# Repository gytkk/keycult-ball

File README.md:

# keycult-ball

Keycult No.1/60에 트랙볼을 결합하기 위한 PCB와 보강판(플레이트)을 제작하는 개인 프로젝트입니다. 기존 케이스를 절삭하거나 새 구멍을 뚫지 않고, PCB와 보강판을 교체해 G/H 사이에 34mm Keyball을 배치하는 것이 목표입니다. 키 배열은 직교 배열을 사용하고, 유선 USB와 QMK 기반 키보드 및 포인팅 장치를 구현할 계획입니다.

현재는 예비 기구 배치와 **65키 및 62키 KiCad 회로도·PCB 배선 초안**을 검토하는 단계입니다. DRAFT E는 외부 조립체 DB1로 UDB C5-JSH를 그대로 사용하며, 하단 1.5u M1/M2 좌표에 맞춰 내부 회로와 매트릭스 배선을 다시 생성합니다. J1 측 USB는 F.Cu 중심 배선과 접지 귀환 경로를 적용합니다. JLC04161H-7628 후보 stackup을 CAD에 명시하고 접지 귀환 경로를 보완했으며, [USB 배선 검토](design/pcb/README.md#usb-routing-findings)에 적용 범위와 한계를 기록합니다. [KiCad 프로젝트 안내](design/pcb/README.md), 배치도, 키 중심 좌표 및 1:1 인쇄 자료가 있으며, 현재 검사 결과는 [65키 보고서](design/pcb/reports/validation.json)와 [62키 보고서](design/pcb/62/reports/validation.json)를 기준으로 합니다. 실제 케이스 조립, 센서 인터페이스, 전원 및 USB 신호 품질과 제조 적합성은 미확정입니다. 제조용 최종 CAD나 빌드·동작 검증된 QMK 펌웨어는 아직 없습니다.

보유 케이스는 NovelKeys 최신 판매 버전의 WK이며, 정확한 리비전과 과거 공개 도면의 호환성은 확인이 필요합니다. G/H 사이 중앙 통합은 필수 조건이며 외부 별도 장치는 범위에서 제외합니다. 34mm Keyball은 현재 예비 배치의 기준이고, 작은 볼과 터치패드도 중앙 통합 후보로 검토합니다. 최종 장치는 아직 선택하지 않았으며 [실현 가능성과 대안 조사](docs/feasibility.md)를 참고합니다.

[로컬 FreeCAD 보강판 초안](design/preliminary/design.md#로컬-freecad-보강판-초안)은 공식 NoLeaf 외곽에 65키·62키 좌표를 적용해 재생성하고 중앙 개구와 네 점으로 고정하는 프레임을 검토합니다. 편집용 FCStd와 STEP/DXF는 원본 사용 조건에 따라 로컬에만 생성합니다. 설명용 볼 높이에서 현재 PCB와 간섭하므로 제조용 도면은 아니며, 홀더·센서의 실제 고정부와 PCB 개구 또는 볼 높이를 추가로 결정해야 합니다. [FreeCAD 실행 및 재현 절차](docs/reproduction.md#freecad-보강판-초안)를 따릅니다.

## 현재 검토 중인 배치

추천안은 15u 너비의 5행 65키 배열이며, 중앙 3열의 가운데 3행을 비워 트랙볼 공간을 확보합니다. 하단 중앙은 1.5u M1/M2 두 키로 총 3u를 차지하며 M3 물리 키는 제거합니다. 실제 키캡과 스위치 조립 적합성은 미확정입니다. 아래 값은 현재 예비 설계의 계산값입니다.

| 항목 | 값 또는 조건 |
| --- | --- |
| 키 피치와 명목 키필드 | 19.05mm, 285.75 × 95.25mm |
| 볼과 G/H 키 중심 | 볼 `(0, 0)`, G `(-38.10, 0)`, H `(+38.10, 0)`, 단위 mm |
| 볼과 키캡 사이 최소 평면 간격 | 지름 34mm 볼과 1u 18 x 18mm, 1.5u 27.525 x 18mm 키캡 가정에서 12.10mm |
| 임시 조립 예약 영역 | 50 × 50mm, 키캡과 최소 4.10mm 간격 |
| 뒤쪽 공간 확보 옵션 | 15u 62키. 상단 중앙 Vol-/Mute/Vol+를 제거해 중앙 명목 빈 영역을 57.15 × 76.20mm로 확장 |
| 보류한 대안 | 14u 너비의 64키 배열. 같은 예약 영역과 키캡이 5.425mm 겹침 |

62키 옵션은 볼 지름 34mm와 중심, G/H 및 하단 1.5u M1/M2를 포함한 나머지 키를 유지합니다. 뒤쪽 한 행을 비워 센서와 배선, 지지 브리지와 체결 간격을 검토할 공간을 확보합니다. 키 제거만으로 강성이 좋아지는 것은 아니며, 빈 영역 전체를 절개하면 강성이 낮아질 수 있습니다. 볼을 키우거나 수직 여유를 늘리는 옵션이 아닙니다.

KiCad 원본은 65키의 `design/pcb/keycult65.*`와 62키의 `design/pcb/62/keycult62.*`로 나눕니다. 두 PCB의 MCU·전원 등 공통 회로는 이전 초안에서 왼쪽으로 76.2mm(4피치) 옮겨 뒤쪽 중앙 빈 영역을 피합니다. 65키 PCB는 중앙 50 x 50mm를 예약하고, 62키 PCB는 명목 빈 영역을 작업 외곽에 맞춰 자른 57.15 x 75.875mm를 부품·구리 금지 영역으로 둡니다. 두 영역 모두 실제 가공 구멍이나 홀더 치수가 아니며, 중앙 Edge.Cuts 개구는 없습니다. 예비 배치와 PCB는 같은 키 좌표를 사용합니다.

50 × 50mm 영역은 실제 홀더 외곽이나 보강판 및 PCB의 가공 구멍 치수가 아닙니다. 공개 도면의 초록색 경계도 공식 보강판 윤곽을 복제한 것이 아니라, 전체 치수만 참조한 285.75 × 108.25mm 직사각형입니다. 현재 검증은 이 경계 안의 포함 여부와 부품 사이 평면 간격을 확인하며, 실제 케이스 개구부 통과나 수직 공간, 조립 가능 여부를 증명하지 않습니다.

## 자료 안내

| 자료 | 내용 |
|---|---|
| [프로젝트 맥락](docs/project-context.md) | 요구사항, 결정 이유, 확정/가정/미확정, 실측·다음 단계 |
| [KiCad 65키·62키 초안](design/pcb/README.md) | 각 배열의 편집 가능한 회로도·PCB, BOM·GPIO 맵, 실제 ERC/DRC·좌표 검증 및 PDF/SVG |
| [PCB 구현 계획](docs/pcb-implementation-plan.md) | 실측 전에 진행할 회로도·PCB 초안, 단계별 산출물과 제조 전 검증 |
| [실현 가능성과 대안 조사](docs/feasibility.md) | 34mm 중앙 통합의 제약과 중앙에 통합할 소형 터치패드·트랙볼 비교 |
| [상세 설계와 출처](design/preliminary/design.md) | 치수 계산, 장착·flex, 센서 방향, QMK·USB 범위 |
| [Ploopy / Keyball / Charybdis 및 라이선스](docs/alternatives-and-licenses.md) | 제품별 차이, 원본 공개 범위와 재사용 조건 |
| [배치 HTML](design/preliminary/layout.html) · [SVG](design/preliminary/layout.svg) · [JSON](design/preliminary/layout.json) | 브라우저 설명도, 편집 가능한 벡터, 모든 키 중심 좌표 |
| [단면 SVG](design/preliminary/section.svg) · [PNG](design/preliminary/section.png) | 수직 설치 센서와 미확정 Z 스택 |
| [1:1 A3 PDF](design/preliminary/print-1to1.pdf) · [SVG](design/preliminary/print-1to1.svg) | 100mm 기준선 포함 종이 검증용 |
| [62키 옵션 SVG](design/preliminary/rear-clearance.svg) · [PNG](design/preliminary/rear-clearance.png) · [1:1 A3 PDF](design/preliminary/rear-clearance-print.pdf) · [인쇄 SVG](design/preliminary/rear-clearance-print.svg) · [인쇄 HTML](design/preliminary/rear-clearance-print.html) | 뒤쪽 공간 확보 비교. 좌표는 `layout.json`의 `rear_clearance` |
| [재현·검증 방법](docs/reproduction.md) | 좌표 생성, PNG/PDF 렌더, 원본 취득·해시 검증 |
| [에이전트 작업 지침](AGENTS.md) | 설계 변경, 검증, 공개 자료 관리, 커밋·푸시 규칙 |

HTML은 저장소를 내려받은 뒤 브라우저에서 엽니다. GitHub에서는 위 PNG로 미리 볼 수 있습니다. 종이 배치는 A3 가로, 배율 100%, 페이지 맞춤을 끈 상태로 출력하고 100mm 기준선을 자로 확인합니다.

## 생성과 검증

Python 3.11 이상과 `uv`를 사용하며, 명령은 저장소 루트에서 실행합니다. 검증 및 렌더 스크립트의 의존성은 각 파일의 메타데이터에 고정되어 있고 `uv run`이 준비합니다.

기존 산출물과 문서의 로컬 링크를 검증하려면 다음 명령을 실행합니다.

```bash
uv run scripts/validate.py
```

배열이나 치수를 변경한 경우에는 산출물을 순서대로 다시 생성하고 검증합니다.

```bash
uv run design/preliminary/build_artifacts.py
uv run scripts/render.py
uv run scripts/validate.py
```

`design/preliminary/build_artifacts.py`의 배열과 치수 상수가 편집 원본이며, 키 중심 JSON과 SVG/HTML은 생성 결과입니다. 설계 변경은 생성기에 반영합니다. 생성기만 실행하면 기존 PNG/PDF는 갱신되지 않으므로 `scripts/render.py`도 실행해야 합니다. 렌더에는 시스템 Chromium이 필요하며, PATH에서 찾을 수 없으면 `KEYCULT_CHROMIUM`에 실행 파일의 절대 경로를 지정합니다.

검증 스크립트는 파일 형식과 로컬 링크, 키 개수와 좌표, 평면 간격, 직사각형 경계 안의 포함 여부, PDF의 A3 크기와 100mm 기준선을 검사합니다. 검증 결과 일부는 `envelope-containment.json`과 `print-validation.json`에 기록됩니다.

공식 윤곽 검사는 별도 절차입니다. 원본 사용 조건을 확인한 뒤 `uv run scripts/fetch_sources.py`로 원본을 취득하고 `uv run scripts/verify_official_contour.py`로 재현합니다. [과거 검사 기록](design/preliminary/plate-containment.json)은 현재 공개 검증으로 갱신되지 않습니다. 추출 좌표와 재검사 출력의 저장 위치, 해시 확인 방법은 [재현 문서](docs/reproduction.md)를 따릅니다.

## 다음 설계 단계

1. [65키·62키 KiCad 초안](design/pcb/README.md)의 실제 ERC/DRC와 미배선 보고서를 검토하고, USB·클록·전원 배선 품질을 보완합니다. GH60의 285.0 x 94.6mm 요약 치수를 작업 외곽으로 사용하며 배열별 중앙 예약 영역에 부품과 구리를 두지 않습니다. USB는 UDB C5-JSH와 적절한 길이의 1:1 케이블을 사용하는 설계 가정으로 진행하고, 조립 전에 커넥터와 케이스 공간 및 케이블 도통을 확인합니다. 센서는 정확한 사양이 확인될 때까지 논리 패드로 남깁니다.
2. QMK 핀맵과 펌웨어 빌드를 병행하고, 실물 부품과 배선 조건이 확인되면 단일 USB 동작을 시험합니다.
3. 후속 실측과 종이 배치 검토를 반영해 중앙 개구, 커넥터와 부품 높이 및 장착 구조를 확정합니다. 볼과 센서는 같은 강체에 고정하고, 기구 시제품 검증 후 최종 배선과 제조 데이터를 완성합니다.

측정할 항목과 결정 이유는 [프로젝트 맥락](docs/project-context.md)에 기록합니다. 예비 SVG를 제조용 도면으로 사용하지 않습니다.

## 범위와 출처 관리

공개 자료는 독립 키 배열, 형상을 복제하지 않는 요약 측정값, 검증 결과, 출처 URL과 해시입니다. 제3자 STEP/DXF/Gerber 원본, 공식 보강판 윤곽 좌표와 이를 복제한 도면은 공개하지 않습니다. 원본 다운로드는 `design/preliminary/sources/upstream/`에, 상세 윤곽과 로컬 검사 결과는 `design/preliminary/sources/local/`에 저장하며 두 디렉토리는 Git에서 제외합니다. 원본 대화, 개인 메모, 인증 정보도 포함하지 않습니다.

저장소 공개 자체가 제3자 자료의 재사용이나 재배포 허가를 뜻하지 않습니다. 자료를 취득하거나 재사용하기 전에 [자료별 라이선스와 배포 범위](docs/alternatives-and-licenses.md), [출처와 측정 기록](design/preliminary/sources/README.md)을 확인합니다.

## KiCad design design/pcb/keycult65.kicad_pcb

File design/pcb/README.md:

# Keycult65 and Keycult62 KiCad designs

**DRAFT E, not for fabrication or assembly.** Both variants use the same RP2040 circuit and stable key references. Open the corresponding project in **KiCad 10.0.7**. The schematic and PCB are native editable CAD.

| Variant | Project | Schematic | PCB | Validation |
| --- | --- | --- | --- | --- |
| 65 keys | [keycult65.kicad_pro](keycult65.kicad_pro) | [Schematic](keycult65.kicad_sch) | [PCB](keycult65.kicad_pcb) | [Report](reports/validation.json) |
| 62 keys | [keycult62.kicad_pro](62/keycult62.kicad_pro) | [Schematic](62/keycult62.kicad_sch) | [PCB](62/keycult62.kicad_pcb) | [Report](62/reports/validation.json) |

Both variants pass strict validation after regeneration and saved-route replay: zero ERC violations, DRC violations, unconnected items and schematic/PCB mismatches. The reports contain the counts and CAD hashes. Static electrical checks do not establish powered operation or case fit. The user-approved design assumption is an unmodified external UDB C5-JSH, represented by DB1 in the schematic and assembly BOM, with no footprint on the main PCB. J1 implements its 1:1 cable interface. The sensor interface remains logical pads pending hardware identification.

## Review entry points

- [Native schematic](keycult65.kicad_sch), [native PCB](keycult65.kicad_pcb), [project](keycult65.kicad_pro).
- [Schematic PDF](exports/schematic.pdf), [front copper SVG](exports/front.svg), [back copper SVG](exports/back.svg), [ground plane SVG](exports/ground.svg), [layer PDF](exports/board-layers.pdf).
- 62-key exports: [schematic PDF](62/exports/schematic.pdf), [front](62/exports/front.svg), [back](62/exports/back.svg), [ground plane](62/exports/ground.svg), [layer PDF](62/exports/board-layers.pdf), [BOM](62/bom.csv), [key/GPIO map](62/gpio-map.csv).
- [Real validation summary](reports/validation.json), [KiCad ERC](reports/erc.json), [KiCad DRC including native schematic parity](reports/drc.json), [actual exported netlist](reports/netlist.xml).
The layer PDF is auto-fitted for review, **not a 1:1 print or manufacturing template**.

- [BOM with candidates/uncertainties](bom.csv), [key/GPIO map](gpio-map.csv), [QMK pin reference](qmk-config.h.example), [source/license record](sources.md).

## Implemented electrical content

65 or 62 MX PCB-mount solder switches and individual 1N4148W diodes. Cathode/pad 1 is
the ROW net; current path is COL → switch → diode anode → cathode → ROW. QMK
`COL2ROW`, five rows × fifteen columns; ten intersections are absent in the 65-key variant and thirteen in the 62-key variant. IDs, not labels, identify keys because labels repeat.

Both variants omit bottom-row SW59/D59 and retain SW58/D58 and SW60/D60 as the 1.5u M1/M2 keys, preserving IDs r4c6/r4c8 and removing r4c7. Their layout centres are (-14.2875,38.1)mm and (14.2875,38.1)mm, occupying a combined nominal 3u. The M3 physical key has no replacement mapping yet. The 62-key variant also omits SW7-SW9 and D7-D9 without renumbering other parts. COL6 and COL8 remain connected to the bottom keys; COL7 has no key in the 62-key variant, so GP16 is marked NC in its schematic. The shared 15-column GPIO ordering is retained; all COL7 matrix cells must be KC_NO in eventual firmware. Removing only the three switches from a functioning 65-key board leaves open matrix cells; map those positions to `KC_NO` in the eventual firmware. Cutting the PCB is a separate mechanical and copper change, never implied by switch removal.

RP2040 is directly mounted in its 7×7mm QFN, not represented by a development
board. The design includes AP2112K-3.3, input PTC, input/output bulk capacitors,
individual IOVDD/ADC/USB/core decoupling, the internal 1.1V regulator's 1µF caps,
W25Q16JVSSIQ QSPI flash, QSPI clock resistor, CS pull-up, BOOTSEL through 1kΩ,
12MHz ABM8-272-T3 oscillator with 15pF load caps and 1kΩ drive resistor, USB 27Ω
series resistors, RUN pull-up/reset button, and individual SWD pads. TESTEN is
GND. Unused GPIOs and regulator NC have explicit no-connect marks.

**W25Q16JVSSIQ uses the 208mil/5.3mm SOIC footprint**, not a similarly named
150mil SOIC. Passive MPNs, capacitor bias derating, crystal drive/startup and
supply thermal/load budgets remain a procurement/bring-up review, not claims of
qualification. No power LED was added. PTC hold rating does not authorize a
500mA USB device or prove USB descriptor/inrush compliance.

### GPIO budget

| Purpose | RP2040 GPIO |
|---|---|
| SPI0 MISO / CS / SCLK / MOSI | GP0 / GP1 / GP2 / GP3 |
| Rows 0–4 | GP4, GP5, GP6, GP7, GP8 |
| Columns 0–14 | GP9–GP22, GP26; GP16/COL7 is NC in the 62-key variant |
| Optional sensor motion / reset | GP23 / GP24 |
| Explicit unused/NC | GP25 / GP27 / GP28 / GP29; also GP16 in the 62-key variant |

The 65-key variant allocates 26 of 30 GPIOs, including two optional sensor controls; four remain
unused. The 62-key variant allocates 25, leaving five NC. Dedicated QSPI, USB and SWD pins do not consume these 30 GPIOs.
`qmk-config.h.example` is a mapping aid, **not a compiled QMK port**. It does not
select a sensor revision, flash boot stage, descriptor power or a final keymap.

## USB daughterboard interface and compatibility limits

**J1 is a JST SM04B-SRSS-TB(LF)(SN), a 4-contact, 1.00mm-pitch side-entry header on B.Cu.** The [Wilba WT60-D product documentation](https://salvun.com/products/wilba-60-pcb-wt60-d) explicitly identifies its JST connection as UDB-compatible and lists Keycult No.1/60 compatibility after removing the on-board USB connector and fitting JST. The [UDB designer specification](https://github.com/Unified-Daughterboard/UDB-C-Legacy/wiki/PCB-side-design-resources) and [pinned C3 schematic](https://github.com/Unified-Daughterboard/UDB-C-Legacy/blob/2ecdd7e0482ecbd3ffe9af04966ab3555f7fc33c/KiCad/C3/Unified-Daughterboard.sch) establish the connector and pinout. This supports the UDB electrical design target; it does not identify the user's uninspected daughterboard as a particular UDB revision.

| J1 contact | Signal | Existing test pad |
| --- | --- | --- |
| 1 | VBUS_USB, after C5-JSH protection and before main-board F1 | TP1 |
| 2 | USB_DM, D- | TP3 |
| 3 | USB_DP, D+ | TP4 |
| 4 | GND | TP2 |
| MP | Mechanical solder anchors, tied to GND locally | Not a cable contact |

Use a **1:1 contact-number cable**, 1-to-1 through 4-to-4. Wire color and apparent left-to-right order are not pin-number evidence. TP1-TP4 retain their earlier numbering and are test access, not the connector's contact order. The validator independently checks J1 against the UDB map, including rejection of reversed power and swapped data contacts.

J1's footprint origin is PCB **(40.6,112.0)mm**, B.Cu, rotation 90 degrees, with its mouth facing keyboard-left. Looking down from the switch side, pad centres are x=42.6mm and y=113.5,112.5,111.5,110.5mm for contacts 1-4. The [official WT60-A photo](https://keycult.com/products/wt60-a-pcb-60) supports a left-edge connector facing outward, but supplies no exact coordinates. Our position is an independent placement between the ortholinear switch/diode footprints, **not a measured WT60-A connector registration**. Case-channel alignment, mating clearance and the connector's full installed height below the PCB need physical checking. JST specifies a nominal 2.9mm body height; do not infer assembled clearance from the footprint courtyard alone.

J1's data pair runs on F.Cu along the left and top margins, above the In1.Cu ground pour, with short B.Cu escapes at J1, TP3/TP4 and R1/R2. Connector-side USB traces are 0.29mm wide; the paired F.Cu portions have a 0.2mm edge gap. VBUS retains its separate 0.4mm feed to the main-board fuse. The MCU-side USB traces and component placement are unchanged.

The 2026-10-30 resume review measured the saved native PCB segments in both variants. Their USB copper is identical. Lengths below are the sum of segment centreline lengths, including branches to test pads; they exclude pad traversal, via barrels and the external cable, so they are not end-to-end electrical lengths.

| Saved copper | D- | D+ |
| --- | --- | --- |
| J1-side net, before the series resistor | 151.4028mm | 157.3721mm |
| F.Cu portion of J1-side net | 146.5028mm | 150.4615mm |
| B.Cu portion of J1-side net | 4.9000mm | 6.9107mm |
| Vias on the J1-side net | 4 | 4 |
| MCU-side net, after the series resistor | 6.6253mm | 6.6253mm |

The J1-side segment-sum difference is 5.9693mm. These are measured routing properties, not acceptance limits or evidence of signal-integrity failure. A USB netclass records the 0.29mm width and 0.2mm gap for these two nets. The candidate dielectric model and the limits of the impedance calculation are described under [USB routing findings](#usb-routing-findings).

Strict validation refills zones and checks the full-width projection of every F.Cu USB segment against the saved In1.Cu GND polygons. Both variants have zero uncovered area outside explicit 0.51mm-radius disks around USB transition vias. Those disks exclude signal-via antipads, not unrelated voids elsewhere on the route. The measured minimum F.Cu pair edge gap is 0.2mm. The layer PDF supports inspection of the J1 escape, margin pair, test pads, resistor transitions and ground fill. These geometric checks do not qualify finite plane edges, transitions or cable discontinuities.

DRAFT E uses a regenerated base route for the current 1.5u M1/M2 coordinates. After SES import, `scripts/usb_routing.py` applies the connector-side USB recipe and ground changes. Validation uses official KiCad 10.0.7 in a local Docker container. The route manifest includes this script's hash. Native schematic parity, external DB1 netlist, coordinates and central reservations are checked again. Both variants have fresh native PDF/SVG exports and validation reports.

DB1 is the unmodified [C5-JSH at revision `2b6c52aa2de6f9f60ca99c6250e4bdf01e8f4eea`](https://github.com/Unified-Daughterboard/UDB-C-JSH/blob/2b6c52aa2de6f9f60ca99c6250e4bdf01e8f4eea/UDB.kicad_sch), adopted as a design assumption on 2026-10-30. Its USB-C connector, two 5.1k CC pull-downs, TPD4E05U06DQAR data-line ESD array, ASMD1206-150 PTC and SMF6.0A TVS stay on the external daughterboard. Its shield joins signal ground on that board; no extra shield wire, CC resistors or duplicate ESD/TVS array is added to the main PCB. This assumption is not a measurement of the factory Keycult board.

Main-board F1 remains a 500mA-hold PTC for local protection, and R1/R2 remain the RP2040's 27-ohm USB series resistors. The two PTCs are in series, so their total voltage drop, trip coordination and actual load/inrush need verification. The TVS suppresses transients; this design has no active sustained-overvoltage disconnect. DB1's BOM row is an external assembly requirement, not a component to populate on the main PCB.

The WT compatibility research supports continuing with the existing J1 pin map. [WT60-C's product documentation](https://dailyclack.com/products/wt60-c-kate-60-pcb) explicitly specifies the same JST part and UDB compatibility; WT60-D does likewise for the interface, and the [Keycult FAQ](https://resources.keycult.com/faq_keycult_faq.html) lists WT60-G for No.1/60. This evidence establishes the design interface without requiring a measurement of the stock cable. It does not establish that every WT-family or Keycult daughterboard contains the same protection components. [Pinned circuit evidence](sources.md#usb-daughterboard-evidence) records the UDB revision differences.

As confirmed by the user on 2026-10-30, a suitable cable length can be sourced; stock-cable reach is no longer a design constraint. Before powered assembly, verify the selected cable's four contact paths and that the assembled external board matches the assumed C5-JSH design. Connector insertion, routing and bend clearance remain mechanical checks in issue #3. Factory-board identification is not a prerequisite for circuit design under this explicit assumption.

## Power and USB desk review

The 2026-10-30 [calculated report](reports/electrical-review.json) records conditional power estimates and native measurements for both boards. It is separate from ERC/DRC and grants no electrical or manufacturing pass. [Primary sources](sources.md#electrical-desk-review-sources) identify the component revisions and public stackups. DRAFT E applies the 7628 routing-study geometry; the provisional power allocations remain assumptions and do not change components or authorize a particular sensor.

### Power allocation

Use **150mA total on +3V3 as a provisional planning envelope**. Allocate 80mA to RP2040, 25mA to flash and 5mA to other board loads, leaving **40mA for a future 3.3V sensor**. The MCU and miscellaneous numbers are engineering allowances, not guaranteed maxima. Flash current depends on frequency and output loading; the 25mA allowance requires checking the cited conditions and a read clock no greater than 104MHz. A 5V Keyball module cannot be assessed using the 40mA rail allowance directly. Its supply, regulators and level translation remain unresolved.

The model reserves another 1mA for LDO ground current, giving 151mA input before external-board leakage. This is an assumption; AP2112's 80uA maximum is a no-load specification. The configured USB power declaration must cover the final whole-device load. The 110mA main-board allocation does not demonstrate compliance with the 100mA pre-configuration limit. Startup and the 2.5mA suspend limit need separate firmware budgets; no power-switching or suspend implementation is claimed here.

Heat screening assumes 5.5V input, nominal 3.3V output, no upstream voltage drop, 1mA LDO ground current, 50 C local ambient and the datasheet's 184 C/W junction-to-ambient resistance. This resistance is a reference condition, not a measurement of this PCB or the closed case.

| +3V3 load | Calculated LDO loss | Estimated junction temperature |
| --- | --- | --- |
| 100mA | 0.2255W | 91.5 C |
| 150mA | 0.3355W | 111.7 C |
| 200mA | 0.4455W | 132.0 C |
| 300mA | 0.6655W | 172.5 C |

Values beyond device limits indicate unsuitable modeled operating points, not predictions of continued operation. A chosen 125 C planning ceiling permits approximately 183mA under these assumptions, so 150mA retains some modeled margin. At 60 C ambient the 150mA estimate is 121.7 C. Higher final load or temperature requires reconsidering the regulator and layout. The 500mA-hold fuse and 600mA regulator labels are not an available continuous power budget.

The two PTC reference-temperature R1max values sum to 1.03ohm. At 151mA, adding 0.5/1.0/2.0ohm for the remaining internal supply/return path gives drops of 0.231/0.307/0.458V. From an assumed 4.4V at the daughterboard receptacle, the LDO sees approximately 4.169/4.093/3.942V. This is a low-voltage stress scenario, not permission to draw 151mA from a low-power port. External USB cable drop is already represented by receptacle voltage; hot PTC resistance is not bounded by the reference values. Nominal 3.3V plus 0.2V dropout is only a screening threshold. Actual regulation must satisfy the RP2040 USB_VDD minimum of 3.135V and flash supply maximum of 3.6V, among the other component conditions.

Native capacitor sums are 1.0uF on VBUS_FUSED, 2.9uF on +3V3 and 1.2uF on +1V1. They omit external-board/sensor capacitance and do not model tolerance, DC bias, regulator startup or active current. Nominal capacitor sums cannot establish an inrush pass.

### USB routing findings

Both variants use identical connector-side USB geometry and an explicit JLC04161H-7628 candidate copper/dielectric model: nominal 1.6mm board, 0.035mm outer copper, 0.0152mm inner copper, 0.2104mm outer-to-inner prepreg with Er=4.4, and a 1.065mm core with Er=4.6. The long pair now runs on F.Cu, 0.2104mm above In1.Cu GND. B.Cu escapes total 4.9mm for D- and 6.91mm for D+ and still lack a continuous adjacent reference plane. Their discontinuities remain part of the signal-integrity review.

Three added GND vias at PCB `(38.5,113.2)`, `(113.4,55.7)` and `(118.5,54.7)mm` join local B.Cu ground patches to In1.Cu. The resistor-side transitions use the existing GND via near `(117.312,66.595)mm`. All eight USB vias are within 2.295mm of a GND via. Validation enforces a 3mm project study criterion, not a USB specification limit. Three B.Cu ground patches and the In1.Cu top-boundary extension from y=53.2mm to y=52.96mm are included in the native zone refill and DRC.

The **JLC04161H-7628 model is applied as a routing-study assumption**, not an approved manufacturing order. JLC04161H-3313 remains a comparison only. Approximate uncoated microstrip calculations at 0.2mm edge gap give:

| Candidate | F.Cu width 0.2mm | Trial F.Cu width | Trial differential impedance |
| --- | --- | --- | --- |
| JLC04161H-7628 | 108.7ohm | 0.29mm | 90.3ohm |
| JLC04161H-3313 | 76.9ohm | 0.16mm | 89.2ohm |

The 90.3ohm result applies to an idealized uniform F.Cu section. It omits solder mask, etched trace shape, finite plane edges, nearby copper, tolerances and transitions. The top outer trace edge is only about 0.395mm inside the modeled ground boundary, so finite-plane effects need review. The CAD stackup records copper and dielectric layers only; it does not specify a fabrication mask construction. Obtain fabricator-approved geometry before treating 0.29mm as a final controlled-impedance width. Strict DRC and ground projection checks passed after routing; they do not measure impedance or establish USB compliance.

The remaining electrical work includes fabricator review and firmware startup/suspend budgets. Sensor integration, actual PTC/cable resistance, thermal measurements, inrush and full-speed waveform tests remain open. The eventual cable construction and length must be included in signal-quality validation.

## Sensor interface remains unresolved

**TP10–TP17 are MCU-side 3.3V logical/test pads only.** They are not the Keyball
7-pin connector. There is no 5V sensor feed, no sensor connector and no approved
5V module-to-RP2040 path. Exact module revision, supply, signal levels and the
appropriate translator/interface remain open in issue #2. Do not wire these
pads straight to an unverified sensor. Reset/motion are reserved, not mandatory
PMW3360 connections. The sensor connector is not finalized; J1's electrical routing is complete but its case and cable fit is provisional.

## Geometry and construction assumptions

- Layout `(0,0)` maps to PCB **(180,100)mm**, +X right, +Y toward the bottom row. Coordinates come from `../preliminary/layout.json`, using `preferred.keys` for 65 keys and `rear_clearance.keys` for 62 keys.
- Stock `SW_Cherry_MX_1.00u_PCB` and `SW_Cherry_MX_1.50u_PCB` have their anchor at **electrical pin 1**, not the
  stem. The stem NPTH is local `(-2.54,+5.08)mm`; generation compensates and
  validation reads the actual stem holes. The base pitch is 19.05mm; the two bottom 1.5u key centres are 28.575mm apart.
- Both variants move the common MCU, flash, clock, power and interface-pad group 76.2mm left from the original draft, with decoupler positions adjusted separately. The original SW7-SW9 area contained essential electronics; the original board must not be cut to obtain the 62-key variant.
- The **285.0 × 94.6mm** working rectangle uses only scalar dimensions measured
  from the pinned GH60 PCB. It does **not** copy GH60's rounded corners/holes,
  any Keycult contour, or the 285.75×108.25mm plate reference rectangle.
- The 65-key all-copper-layer rule area is the centred **50 x 50mm** reservation. The 62-key rule area extends across the nominal empty key band, clipped at the board edge: PCB x=151.425..208.575mm, y=52.7..128.575mm, **57.15 x 75.875mm**. Both prohibit footprints, pads, tracks, vias and copper fill. Neither is an Edge.Cuts opening or a measured holder outline. This larger electrical reservation preserves future placement flexibility; mounting and any eventual cutout still require measurements.
- Four copper layers: F.Cu and B.Cu plus In2.Cu carry most signals. In1.Cu carries the GND reference pour outside the reserved centre, with short local +3V3 and COL12 routes beside the MCU. These routes stay away from the USB pair and the filled ground remains connected. Pad/via antipads and the central reservation still require return-path review; this is not an
  impedance-qualified stackup. Bottom SMT electronics coexist
  with top MX switch bodies, with actual drill/courtyard checks. Board thickness
  is nominally 1.6mm in the candidate model, not a verified case height requirement.
- Review rules are 0.15mm clearance/minimum trace, 0.55-0.6mm via copper diameter with 0.3mm drill, and 0.25mm
  hole/copper-edge clearance. These are **draft routing constraints, not a
  selected manufacturer's process approval**. 0.4mm pitch QFN fan-out, solder
  mask, assembly tolerances and stackup need explicit manufacturing review.
- USB routes need a paired 90Ω differential/return-path review against a chosen
  stackup. Mere routed connectivity or DRC clearance does not establish signal
  integrity. QSPI/crystal/decoupling placement and path lengths need layout
  engineering review before a fabrication release.
- [3D check record](reports/3d-review.json) describes the original draft only. Neither revised variant has component-height or case-assembly approval. The current CLI environment omits component 3D libraries.
- STEP models are linked from installed KiCad stock libraries; no Keycult case
  or sensor assembly STEP is redistributed. A valid 2D board does **not** prove
  Z-stack, actuator clearance, cable bend space, assembly access or case fit.

## Reproduction

The initial seed uses KiCad's maintained `pcbnew` API and installed stock
libraries. `sexpdata` serializes the native schematic with stock symbols and applies the deterministic USB overlay to native PCB data. No custom autorouter was written.
Freerouting performs local detailed routing via KiCad's Specctra DSN/SES API.
A small cleanup script removes only KiCad-reported dead-ended copper after zone refill; it never suppresses checks or unconnected nets. Native CAD retains the complete editable route. Each variant's saved SES records the base route for its current key coordinates. `scripts/usb_routing.py` applies the DRAFT E USB and ground changes after seed generation and SES import. Replaying the SES through `route_pcb.py` reproduces the combined route; rerunning the autorouter from a new seed does not replace layout review or guarantee completion.
See [sources](sources.md) for versions, licenses and hashes.

From the repository root, with the Python version matching KiCad's installed binding (the original Nix runtime uses Python 3.14; the official 10.0.7 Docker image uses Python 3.13). Scripts require Python 3.11 or newer, but `pcbnew` must match the chosen interpreter. Use the [Docker procedure](../../docs/reproduction.md#docker에서-kicad-검증) when KiCad is not installed on the host.

```bash
uv run --python "$(command -v python3)" scripts/build_pcb.py --keys 65
uv run --python "$(command -v python3)" scripts/route_pcb.py --keys 65 --import-saved
uv run --python "$(command -v python3)" scripts/validate_pcb.py --keys 65
uv run --python "$(command -v python3)" scripts/build_pcb.py --keys 62
uv run --python "$(command -v python3)" scripts/route_pcb.py --keys 62 --import-saved
uv run --python "$(command -v python3)" scripts/validate_pcb.py --keys 62
uv run scripts/test_pcb_validation_gate.py
uv run scripts/validate.py
```

**Regeneration overwrites the current CAD seed.** The delivered native CAD is the
review/edit surface; preserve manual edits before rebuilding. The preliminary
layout generator remains the source for key coordinates. A changed layout
requires a new seed, route and inspection, not reuse of an old route snapshot.
The saved route is a reproducible initial draft, not a promise that arbitrary
edits autoroute the same way. Validation writes actual check reports and native
SVG/PDF exports; it does not mask or exclude violations. Running validation
without `--draft` returns nonzero for *any* DRC finding or unconnected item.

## Independent layout review findings

- The original draft had 57 unconnected items across 27 nets. Both revised variants complete the internal circuit and matrix routing, with zero unconnected items after rebuilding and replaying their saved copper.
- The original C13/C14 placement was 16.60/17.52mm from the MCU supply pads; these capacitors and the core decouplers have been repositioned beside their actual rotated supply pins.
- F1's MF-PSMF050X-2 candidate requires an 0805 land pattern; the original 1206 footprint has been corrected.
- USB impedance and return paths still require review against a selected stackup and the actual daughterboard/cable before bring-up. Connectivity alone is not signal-integrity qualification.
- The exposed MCU ground pad has a 0.3mm ground via. Via tenting/filling and solder-paste process must be agreed with the assembler to control solder loss; static DRC does not qualify QFN assembly.
- Local In1.Cu exceptions use 0.15mm traces: +3V3 runs `(102.32,64) -> (103,64.25) -> (106.2,64.25) -> (106.979,65.6)`; COL12 escapes through `(102.35,67.25) -> (102.35,65.5) -> (101.8,64.8) -> (98.7,64.8)`, in PCB mm. The signal is a keyboard column, not USB or QSPI. These short routes trade local ground-plane area for feasible QFN escape routing; the connected pour and USB reference region must be preserved in later edits.
- Draft validation permits unfinished connections only. Any geometric DRC
  finding fails in both strict and draft modes.

## Release gates still open

Issues #1–#6 remain the mechanical/interface/bring-up gate. No Gerber fabrication
release, production BOM, final sensor connector, module-level translator, firmware
build, USB/keyboard/sensor bench test or assembly-fit approval is supplied.
Read the exact outstanding electrical/route counts in each variant's `reports/validation.json`;
a zero ERC or a matching netlist is not a manufacturing-ready assertion.

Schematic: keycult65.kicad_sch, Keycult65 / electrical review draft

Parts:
C1, C2: 1uF; C_0603_1608Metric
C3, C4, C5, C6, C7, C8, C9, C10, C11, C12, C15: 100nF; C_0402_1005Metric
C13, C14: 1uF; C_0402_1005Metric
C16, C17: 15pF; C_0402_1005Metric
D1, D2, D3, D4, D5, D6, D7, D8, D9, D10, D11, D12, D13, D14, D15, D16, D17, D18, D19, D20, D21, D22, D23, D24, D25, D26, D27, D28, D29, D30, D31, D32, D33, D34, D35, D36, D37, D38, D39, D40, D41, D42, D43, D44, D45, D46, D47, D48, D49, D50, D51, D52, D53, D54, D55, D56, D57, D58, D60, D61, D62, D63, D64, D65, D66: 1N4148W; D_SOD-123
DB1: UDB C5-JSH / EXTERNAL
F1: 500mA hold / provisional; Fuse_0805_2012Metric
J1: USB / C5-JSH JST-SH; JST_SH_SM04B-SRSS-TB_1x04-1MP_P1.00mm_Horizontal
R1, R2, R7: 27R; R_0402_1005Metric
R3, R5, R8: 10k; R_0402_1005Metric
R4, R6: 1k; R_0402_1005Metric
SW1: r0c0 Esc; SW_Cherry_MX_1.00u_PCB
SW2: r0c1 1; SW_Cherry_MX_1.00u_PCB
SW3: r0c2 2; SW_Cherry_MX_1.00u_PCB
SW4: r0c3 3; SW_Cherry_MX_1.00u_PCB
SW5: r0c4 4; SW_Cherry_MX_1.00u_PCB
SW6: r0c5 5; SW_Cherry_MX_1.00u_PCB
SW7: r0c6 Vol-; SW_Cherry_MX_1.00u_PCB
SW8: r0c7 Mute; SW_Cherry_MX_1.00u_PCB
SW9: r0c8 Vol+; SW_Cherry_MX_1.00u_PCB
SW10: r0c9 6; SW_Cherry_MX_1.00u_PCB
SW11: r0c10 7; SW_Cherry_MX_1.00u_PCB
SW12: r0c11 8; SW_Cherry_MX_1.00u_PCB
SW13: r0c12 9; SW_Cherry_MX_1.00u_PCB
SW14: r0c13 0; SW_Cherry_MX_1.00u_PCB
SW15: r0c14 Bksp; SW_Cherry_MX_1.00u_PCB
SW16: r1c0 Tab; SW_Cherry_MX_1.00u_PCB
SW17: r1c1 Q; SW_Cherry_MX_1.00u_PCB
SW18: r1c2 W; SW_Cherry_MX_1.00u_PCB
SW19: r1c3 E; SW_Cherry_MX_1.00u_PCB
SW20: r1c4 R; SW_Cherry_MX_1.00u_PCB
SW21: r1c5 T; SW_Cherry_MX_1.00u_PCB
SW22: r1c9 Y; SW_Cherry_MX_1.00u_PCB
SW23: r1c10 U; SW_Cherry_MX_1.00u_PCB
SW24: r1c11 I; SW_Cherry_MX_1.00u_PCB
SW25: r1c12 O; SW_Cherry_MX_1.00u_PCB
SW26: r1c13 P; SW_Cherry_MX_1.00u_PCB
SW27: r1c14 \; SW_Cherry_MX_1.00u_PCB
SW28: r2c0 Caps; SW_Cherry_MX_1.00u_PCB
SW29: r2c1 A; SW_Cherry_MX_1.00u_PCB
SW30: r2c2 S; SW_Cherry_MX_1.00u_PCB
SW31: r2c3 D; SW_Cherry_MX_1.00u_PCB
SW32: r2c4 F; SW_Cherry_MX_1.00u_PCB
SW33: r2c5 G; SW_Cherry_MX_1.00u_PCB
SW34: r2c9 H; SW_Cherry_MX_1.00u_PCB
SW35: r2c10 J; SW_Cherry_MX_1.00u_PCB
SW36: r2c11 K; SW_Cherry_MX_1.00u_PCB
SW37: r2c12 L; SW_Cherry_MX_1.00u_PCB
SW38: r2c13 ;; SW_Cherry_MX_1.00u_PCB
SW39: r2c14 Enter; SW_Cherry_MX_1.00u_PCB
SW40: r3c0 Shift; SW_Cherry_MX_1.00u_PCB
SW41: r3c1 Z; SW_Cherry_MX_1.00u_PCB
SW42: r3c2 X; SW_Cherry_MX_1.00u_PCB
SW43: r3c3 C; SW_Cherry_MX_1.00u_PCB
SW44: r3c4 V; SW_Cherry_MX_1.00u_PCB
SW45: r3c5 B; SW_Cherry_MX_1.00u_PCB
SW46: r3c9 N; SW_Cherry_MX_1.00u_PCB
SW47: r3c10 M; SW_Cherry_MX_1.00u_PCB
SW48: r3c11 ,; SW_Cherry_MX_1.00u_PCB
SW49: r3c12 .; SW_Cherry_MX_1.00u_PCB
SW50: r3c13 /; SW_Cherry_MX_1.00u_PCB
SW51: r3c14 Shift; SW_Cherry_MX_1.00u_PCB
SW52: r4c0 Ctrl; SW_Cherry_MX_1.00u_PCB
SW53: r4c1 GUI; SW_Cherry_MX_1.00u_PCB
SW54: r4c2 Alt; SW_Cherry_MX_1.00u_PCB
SW55: r4c3 Fn; SW_Cherry_MX_1.00u_PCB
SW56: r4c4 Space; SW_Cherry_MX_1.00u_PCB
SW57: r4c5 Del; SW_Cherry_MX_1.00u_PCB
SW58: r4c6 M1; SW_Cherry_MX_1.50u_PCB
SW60: r4c8 M2; SW_Cherry_MX_1.50u_PCB
SW61: r4c9 Bksp; SW_Cherry_MX_1.00u_PCB
SW62: r4c10 Space; SW_Cherry_MX_1.00u_PCB
SW63: r4c11 Fn; SW_Cherry_MX_1.00u_PCB
SW64: r4c12 Left; SW_Cherry_MX_1.00u_PCB
SW65: r4c13 Down; SW_Cherry_MX_1.00u_PCB
SW66: r4c14 Right; SW_Cherry_MX_1.00u_PCB
SW67: BOOTSEL; SW_SPST_TL3342
SW68: RESET; SW_SPST_TL3342
TP1: VBUS_USB / USB TEST; TestPoint_Pad_D1.5mm
TP2: GND / USB TEST; TestPoint_Pad_D1.5mm
TP3: USB_DM / USB TEST; TestPoint_Pad_D1.5mm
TP4: USB_DP / USB TEST; TestPoint_Pad_D1.5mm
TP5: SWCLK / SWD; TestPoint_Pad_D1.0mm
TP6: SWDIO / SWD; TestPoint_Pad_D1.0mm
TP7: RUN / SWD; TestPoint_Pad_D1.0mm
TP8: GND / SWD; TestPoint_Pad_D1.0mm
TP9: +3V3 / SWD; TestPoint_Pad_D1.0mm
TP10: SENSOR_MISO_3V3; TestPoint_Pad_D1.0mm
TP11: SENSOR_CS_3V3; TestPoint_Pad_D1.0mm
TP12: SENSOR_SCLK_3V3; TestPoint_Pad_D1.0mm
TP13: SENSOR_MOSI_3V3; TestPoint_Pad_D1.0mm
TP14: SENSOR_MOTION_3V3; TestPoint_Pad_D1.0mm
TP15: SENSOR_RESET_3V3; TestPoint_Pad_D1.0mm
TP16: GND; TestPoint_Pad_D1.0mm
TP17: +3V3; TestPoint_Pad_D1.0mm
U1: RP2040; QFN-56-1EP_7x7mm_P0.4mm_EP3.2x3.2mm
U2: W25Q16JVSSIQ; SOIC-8_5.3x5.3mm_P1.27mm
U3: AP2112K-3.3TRG1; SOT-23-5
Y1: ABM8-272-T3 12MHz CL10pF; Crystal_SMD_3225-4Pin_3.2x2.5mm

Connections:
+1V1: C11.1, C12.1, C14.1, U1.23 (DVDD), U1.45 (VREG_VOUT), U1.50 (DVDD)
+3V3: C2.1, C3.1, C4.1, C5.1, C6.1, C7.1, C8.1, C9.1, C10.1, C13.1, C15.1, R3.1, R5.1, R8.1, TP9.1, TP17.1, U1.1 (IOVDD), U1.10 (IOVDD), U1.22 (IOVDD), U1.33 (IOVDD), U1.42 (IOVDD), U1.43 (ADC_AVDD), U1.44 (VREG_VIN), U1.48 (USB_VDD), U1.49 (IOVDD), U2.8 (VCC), U3.5 (VOUT)
BOOT_SW: R4.2, SW67.1
COL0: SW1.1, SW16.1, SW28.1, SW40.1, SW52.1, U1.12 (GPIO9)
COL1: SW2.1, SW17.1, SW29.1, SW41.1, SW53.1, U1.13 (GPIO10)
COL2: SW3.1, SW18.1, SW30.1, SW42.1, SW54.1, U1.14 (GPIO11)
COL3: SW4.1, SW19.1, SW31.1, SW43.1, SW55.1, U1.15 (GPIO12)
COL4: SW5.1, SW20.1, SW32.1, SW44.1, SW56.1, U1.16 (GPIO13)
COL5: SW6.1, SW21.1, SW33.1, SW45.1, SW57.1, U1.17 (GPIO14)
COL6: SW7.1, SW58.1, U1.18 (GPIO15)
COL7: SW8.1, U1.27 (GPIO16)
COL8: SW9.1, SW60.1, U1.28 (GPIO17)
COL9: SW10.1, SW22.1, SW34.1, SW46.1, SW61.1, U1.29 (GPIO18)
COL10: SW11.1, SW23.1, SW35.1, SW47.1, SW62.1, U1.30 (GPIO19)
COL11: SW12.1, SW24.1, SW36.1, SW48.1, SW63.1, U1.31 (GPIO20)
COL12: SW13.1, SW25.1, SW37.1, SW49.1, SW64.1, U1.32 (GPIO21)
COL13: SW14.1, SW26.1, SW38.1, SW50.1, SW65.1, U1.34 (GPIO22)
COL14: SW15.1, SW27.1, SW39.1, SW51.1, SW66.1, U1.38 (GPIO26/ADC0)
GND: C1.2, C2.2, C3.2, C4.2, C5.2, C6.2, C7.2, C8.2, C9.2, C10.2, C11.2, C12.2, C13.2, C14.2, C15.2, C16.2, C17.2, DB1.4, J1.4, J1.MP (MountPin), SW67.2, SW68.2, TP2.1, TP8.1, TP16.1, U1.19 (TESTEN), U1.57 (GND), U2.4 (GND), U3.2 (GND), Y1.2 (G), Y1.4 (G)
K_r0c0: D1.2 (A), SW1.2
K_r0c1: D2.2 (A), SW2.2
K_r0c2: D3.2 (A), SW3.2
K_r0c3: D4.2 (A), SW4.2
K_r0c4: D5.2 (A), SW5.2
K_r0c5: D6.2 (A), SW6.2
K_r0c6: D7.2 (A), SW7.2
K_r0c7: D8.2 (A), SW8.2
K_r0c8: D9.2 (A), SW9.2
K_r0c9: D10.2 (A), SW10.2
K_r0c10: D11.2 (A), SW11.2
K_r0c11: D12.2 (A), SW12.2
K_r0c12: D13.2 (A), SW13.2
K_r0c13: D14.2 (A), SW14.2
K_r0c14: D15.2 (A), SW15.2
K_r1c0: D16.2 (A), SW16.2
K_r1c1: D17.2 (A), SW17.2
K_r1c2: D18.2 (A), SW18.2
K_r1c3: D19.2 (A), SW19.2
K_r1c4: D20.2 (A), SW20.2
K_r1c5: D21.2 (A), SW21.2
K_r1c9: D22.2 (A), SW22.2
K_r1c10: D23.2 (A), SW23.2
K_r1c11: D24.2 (A), SW24.2
K_r1c12: D25.2 (A), SW25.2
K_r1c13: D26.2 (A), SW26.2
K_r1c14: D27.2 (A), SW27.2
K_r2c0: D28.2 (A), SW28.2
K_r2c1: D29.2 (A), SW29.2
K_r2c2: D30.2 (A), SW30.2
K_r2c3: D31.2 (A), SW31.2
K_r2c4: D32.2 (A), SW32.2
K_r2c5: D33.2 (A), SW33.2
K_r2c9: D34.2 (A), SW34.2
K_r2c10: D35.2 (A), SW35.2
K_r2c11: D36.2 (A), SW36.2
K_r2c12: D37.2 (A), SW37.2
K_r2c13: D38.2 (A), SW38.2
K_r2c14: D39.2 (A), SW39.2
K_r3c0: D40.2 (A), SW40.2
K_r3c1: D41.2 (A), SW41.2
K_r3c2: D42.2 (A), SW42.2
K_r3c3: D43.2 (A), SW43.2
K_r3c4: D44.2 (A), SW44.2
K_r3c5: D45.2 (A), SW45.2
K_r3c9: D46.2 (A), SW46.2
K_r3c10: D47.2 (A), SW47.2
K_r3c11: D48.2 (A), SW48.2
K_r3c12: D49.2 (A), SW49.2
K_r3c13: D50.2 (A), SW50.2
K_r3c14: D51.2 (A), SW51.2
K_r4c0: D52.2 (A), SW52.2
K_r4c1: D53.2 (A), SW53.2
K_r4c2: D54.2 (A), SW54.2
K_r4c3: D55.2 (A), SW55.2
K_r4c4: D56.2 (A), SW56.2
K_r4c5: D57.2 (A), SW57.2
K_r4c6: D58.2 (A), SW58.2
K_r4c8: D60.2 (A), SW60.2
K_r4c9: D61.2 (A), SW61.2
K_r4c10: D62.2 (A), SW62.2
K_r4c11: D63.2 (A), SW63.2
K_r4c12: D64.2 (A), SW64.2
K_r4c13: D65.2 (A), SW65.2
K_r4c14: D66.2 (A), SW66.2
QSPI_SCLK: R7.1, U1.52 (QSPI_SCLK)
QSPI_SCLK_FLASH: R7.2, U2.6 (CLK)
QSPI_SD0: U1.53 (QSPI_SD0), U2.5 (DI/IO_{0})
QSPI_SD1: U1.55 (QSPI_SD1), U2.2 (DO/IO_{1})
QSPI_SD2: U1.54 (QSPI_SD2), U2.3 (~WP/IO_{2})
QSPI_SD3: U1.51 (QSPI_SD3), U2.7 (~HOLD/~RESET/IO_{3})
QSPI_SS: R3.2, R4.1, U1.56 (~QSPI_SS), U2.1 (~CS)
ROW0: D1.1 (K), D2.1 (K), D3.1 (K), D4.1 (K), D5.1 (K), D6.1 (K), D7.1 (K), D8.1 (K), D9.1 (K), D10.1 (K), D11.1 (K), D12.1 (K), D13.1 (K), D14.1 (K), D15.1 (K), U1.6 (GPIO4)
ROW1: D16.1 (K), D17.1 (K), D18.1 (K), D19.1 (K), D20.1 (K), D21.1 (K), D22.1 (K), D23.1 (K), D24.1 (K), D25.1 (K), D26.1 (K), D27.1 (K), U1.7 (GPIO5)
ROW2: D28.1 (K), D29.1 (K), D30.1 (K), D31.1 (K), D32.1 (K), D33.1 (K), D34.1 (K), D35.1 (K), D36.1 (K), D37.1 (K), D38.1 (K), D39.1 (K), U1.8 (GPIO6)
ROW3: D40.1 (K), D41.1 (K), D42.1 (K), D43.1 (K), D44.1 (K), D45.1 (K), D46.1 (K), D47.1 (K), D48.1 (K), D49.1 (K), D50.1 (K), D51.1 (K), U1.9 (GPIO7)
ROW4: D52.1 (K), D53.1 (K), D54.1 (K), D55.1 (K), D56.1 (K), D57.1 (K), D58.1 (K), D60.1 (K), D61.1 (K), D62.1 (K), D63.1 (K), D64.1 (K), D65.1 (K), D66.1 (K), U1.11 (GPIO8)
RUN: R5.2, SW68.1, TP7.1, U1.26 (RUN)
SENSOR_CS_3V3: R8.2, TP11.1, U1.3 (GPIO1)
SENSOR_MISO_3V3: TP10.1, U1.2 (GPIO0)
SENSOR_MOSI_3V3: TP13.1, U1.5 (GPIO3)
SENSOR_MOTION_3V3: TP14.1, U1.35 (GPIO23)
SENSOR_RESET_3V3: TP15.1, U1.36 (GPIO24)
SENSOR_SCLK_3V3: TP12.1, U1.4 (GPIO2)
SWCLK: TP5.1, U1.24 (SWCLK)
SWDIO: TP6.1, U1.25 (SWDIO)
USB_DM: DB1.2, J1.2, R1.2, TP3.1
USB_DM_MCU: R1.1, U1.46 (USB_DM)
USB_DP: DB1.3, J1.3, R2.2, TP4.1
USB_DP_MCU: R2.1, U1.47 (USB_DP)
VBUS_FUSED: C1.1, F1.2, U3.1 (VIN), U3.3 (EN)
VBUS_USB: DB1.1, F1.1, J1.1, TP1.1
XIN: C16.1, U1.20 (XIN), Y1.1
XOUT: R6.1, U1.21 (XOUT)
XOUT_CRYSTAL: C17.1, R6.2, Y1.3

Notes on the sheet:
1 / RP2040 + FLASH + BOOT + RESET
2 / USB DAUGHTERBOARD + 3V3 POWER
3 / CLOCK + SENSOR MCU-SIDE ONLY
No module connector or 5V sensor connection. Verify revision and level translation before connection.
DECOUPLING: individual IOVDD / USB / ADC / DVDD pins; VREG 1uF input + output
4 / 5 ROW x 15 COLUMN MATRIX: COL -> switch -> diode ANODE -> CATHODE -> ROW (COL2ROW)
65 keys; Keycult65. Bottom M1/M2: 1.5u each. Central reservation is NOT A HOLE.
DB1: EXTERNAL C5-JSH assumed; CC 5.1k x2 / TPD4E05U06 ESD / PTC / SMF6.0A TVS.
J1: 1=protected USB power 2=D- 3=D+ 4=GND; 1:1 cable. Main-board F1 retained.
Shield joins GND on DB1. No active sustained-overvoltage disconnect. Mechanical fit provisional.

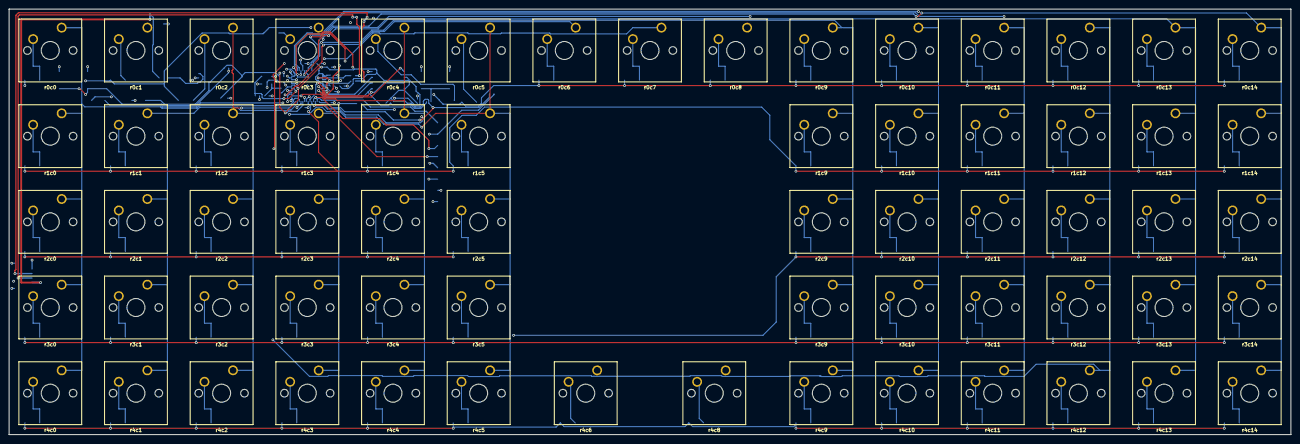
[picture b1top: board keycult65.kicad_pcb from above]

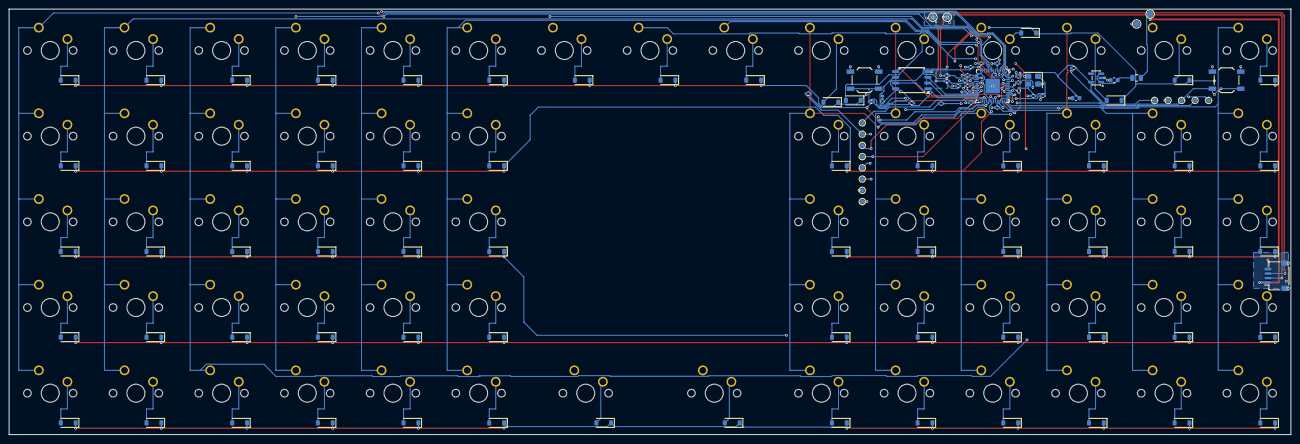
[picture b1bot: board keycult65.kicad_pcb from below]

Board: 4 copper layers, 285.0 x 94.6 mm, 180 parts (115 on the bottom side), 114 nets.

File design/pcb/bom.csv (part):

Reference,Value,Manufacturer part / candidate,Footprint,Assembly,Status,Notes
U1,RP2040,RP2040,Package_DFN_QFN:QFN-56-1EP_7x7mm_P0.4mm_EP3.2x3.2mm,Bottom SMT,provisional sourcing,Direct mounted QFN; exposed pad to GND; unused GP25/27/28/29 NC
U2,W25Q16JVSSIQ,W25Q16JVSSIQ,Package_SO:SOIC-8_5.3x5.3mm_P1.27mm,Bottom SMT,provisional sourcing,"208 mil SOIC, NOT 150mil package; QMK RP2040 flash boot stage must match"
U3,AP2112K-3.3TRG1,AP2112K-3.3TRG1,Package_TO_SOT_SMD:SOT-23-5,Bottom SMT,provisional sourcing,600mA part rating is NOT USB budget; 5V->3V3 thermal/load budget unresolved
J1,USB / C5-JSH JST-SH,JST SM04B-SRSS-TB(LF)(SN),Connector_JST:JST_SH_SM04B-SRSS-TB_1x04-1MP_P1.00mm_Horizontal,Bottom SMT,C5-JSH interface selected; mechanical fit provisional,"1 protected USB power, 2 D-, 3 D+, 4 GND; 1:1 JST-SH cable of suitable length. External DB1 supplies CC/ESD/PTC/TVS; VBUS_USB is after its PTC and before main-board F1"
DB1,UDB C5-JSH / EXTERNAL,Unified Daughterboard C5-JSH,,External assembly,user-approved design assumption; external assembly,"Pinned 2b6c52aa2de6f9f60ca99c6250e4bdf01e8f4eea; 5.1k CC, TPD4E05U06DQAR ESD, ASMD1206-150 PTC, SMF6.0A TVS, direct shield/GND connection; no active sustained-overvoltage disconnect; not fitted on main PCB"
TP1,VBUS_USB / USB TEST,PCB pad,TestPoint:TestPoint_Pad_D1.5mm,Bottom SMT,test access; J1 is the cable connector,Test-pad numbering differs from J1 contact numbering
TP2,GND / USB TEST,PCB pad,TestPoint:TestPoint_Pad_D1.5mm,Bottom SMT,test access; J1 is the cable connector,Test-pad numbering differs from J1 contact numbering
TP3,USB_DM / USB TEST,PCB pad,TestPoint:TestPoint_Pad_D1.5mm,Bottom SMT,test access; J1 is the cable connector,Test-pad numbering differs from J1 contact numbering
TP4,USB_DP / USB TEST,PCB pad,TestPoint:TestPoint_Pad_D1.5mm,Bottom SMT,test access; J1 is the cable connector,Test-pad numbering differs from J1 contact numbering
F1,500mA hold / provisional,Bourns MF-PSMF050X-2,Fuse:Fuse_0805_2012Metric,Bottom SMT,provisional sourcing,"Retained local main-board PTC after C5-JSH PTC; total drop, load/inrush and trip coordination need verification; not a USB current entitlement"
C1,1uF,TBD X7R 10V,Capacitor_SMD:C_0603_1608Metric,Bottom SMT,provisional sourcing,voltage rating >=10V; capacitance under DC bias to verify
C2,1uF,TBD X7R 10V,Capacitor_SMD:C_0603_1608Metric,Bottom SMT,provisional sourcing,voltage rating >=10V; capacitance under DC bias to verify
C3,100nF,TBD X7R 10V,Capacitor_SMD:C_0402_1005Metric,Bottom SMT,provisional sourcing,voltage rating >=10V; capacitance under DC bias to verify; IOVDD1
C4,100nF,TBD X7R 10V,Capacitor_SMD:C_0402_1005Metric,Bottom SMT,provisional sourcing,voltage rating >=10V; capacitance under DC bias to verify; IOVDD10
C5,100nF,TBD X7R 10V,Capacitor_SMD:C_0402_1005Metric,Bottom SMT,provisional sourcing,voltage rating >=10V; capacitance under DC bias to verify; IOVDD22
C6,100nF,TBD X7R 10V,Capacitor_SMD:C_0402_1005Metric,Bottom SMT,provisional sourcing,voltage rating >=10V; capacitance under DC bias to verify; IOVDD33
C7,100nF,TBD X7R 10V,Capacitor_SMD:C_0402_1005Metric,Bottom SMT,provisional sourcing,voltage rating >=10V; capacitance under DC bias to verify; IOVDD42
C8,100nF,TBD X7R 10V,Capacitor_SMD:C_0402_1005Metric,Bottom SMT,provisional sourcing,voltage rating >=10V; capacitance under DC bias to verify; IOVDD49
C9,100nF,TBD X7R 10V,Capacitor_SMD:C_0402_1005Metric,Bottom SMT,provisional sourcing,voltage rating >=10V; capacitance under DC bias to verify; ADC_AVDD43
C10,100nF,TBD X7R 10V,Capacitor_SMD:C_0402_1005Metric,Bottom SMT,provisional sourcing,voltage rating >=10V; capacitance under DC bias to verify; USB_VDD48
C11,100nF,TBD X7R 10V,Capacitor_SMD:C_0402_1005Metric,Bottom SMT,provisional sourcing,voltage rating >=10V; capacitance under DC bias to verify; DVDD23
C12,100nF,TBD X7R 10V,Capacitor_SMD:C_0402_1005Metric,Bottom SMT,provisional sourcing,voltage rating >=10V; capacitance under DC bias to verify; DVDD50
C13,1uF,TBD X7R 10V,Capacitor_SMD:C_0402_1005Metric,Bottom SMT,provisional sourcing,voltage rating >=10V; capacitance under DC bias to verify; VREG_VIN44
C14,1uF,TBD X7R 10V,Capacitor_SMD:C_0402_1005Metric,Bottom SMT,provisional sourcing,voltage rating >=10V; capacitance under DC bias to verify; VREG_VOUT45
C15,100nF,TBD X7R 10V,Capacitor_SMD:C_0402_1005Metric,Bottom SMT,provisional sourcing,voltage rating >=10V; capacitance under DC bias to verify; QSPI flash VCC
R1,27R,TBD 0402 1% 50V,Resistor_SMD:R_0402_1005Metric,Bottom SMT,provisional sourcing,value fixed; manufacturer not selected
R2,27R,TBD 0402 1% 50V,Resistor_SMD:R_0402_1005Metric,Bottom SMT,provisional sourcing,value fixed; manufacturer not selected
R3,10k,TBD 0402 1% 50V,Resistor_SMD:R_0402_1005Metric,Bottom SMT,provisional sourcing,value fixed; manufacturer not selected
R4,1k,TBD 0402 1% 50V,Resistor_SMD:R_0402_1005Metric,Bottom SMT,provisional sourcing,value fixed; manufacturer not selected
R5,10k,TBD 0402 1% 50V,Resistor_SMD:R_0402_1005Metric,Bottom SMT,provisional sourcing,value fixed; manufacturer not selected
R6,1k,TBD 0402 1% 50V,Resistor_SMD:R_0402_1005Metric,Bottom SMT,provisional sourcing,value fixed; manufacturer not selected
R7,27R,TBD 0402 1% 50V,Resistor_SMD:R_0402_1005Metric,Bottom SMT,provisional sourcing,value fixed; manufacturer not selected
Y1,ABM8-272-T3 12MHz CL10pF,ABM8-272-T3,Crystal:Crystal_SMD_3225-4Pin_3.2x2.5mm,Bottom SMT,provisional sourcing,Confirm ESR/drive/startup on assembled board
C16,15pF,TBD C0G 50V,Capacitor_SMD:C_0402_1005Metric,Bottom SMT,provisional sourcing,voltage rating >=10V; capacitance under DC bias to verify
C17,15pF,TBD C0G 50V,Capacitor_SMD:C_0402_1005Metric,Bottom SMT,provisional sourcing,voltage rating >=10V; capacitance under DC bias to verify
SW67,BOOTSEL,E-Switch TL3342F160QG,Button_Switch_SMD:SW_SPST_TL3342,Bottom SMT,provisional sourcing,Backside service access and switch height not mechanically verified
SW68,RESET,E-Switch TL3342F160QG,Button_Switch_SMD:SW_SPST_TL3342,Bottom SMT,provisional sourcing,Backside service access and switch height not mechanically verified
TP5,SWCLK / SWD,PCB pad,TestPoint:TestPoint_Pad_D1.0mm,Bottom SMT,electrically defined; access provisional,
TP6,SWDIO / SWD,PCB pad,TestPoint:TestPoint_Pad_D1.0mm,Bottom SMT,electrically defined; access provisional,
TP7,RUN / SWD,PCB pad,TestPoint:TestPoint_Pad_D1.0mm,Bottom SMT,electrically defined; access provisional,
TP8,GND / SWD,PCB pad,TestPoint:TestPoint_Pad_D1.0mm,Bottom SMT,electrically defined; access provisional,
TP9,+3V3 / SWD,PCB pad,TestPoint:TestPoint_Pad_D1.0mm,Bottom SMT,electrically defined; access provisional,
TP10,SENSOR_MISO_3V3,PCB pad,TestPoint:TestPoint_Pad_D1.0mm,Bottom SMT,3V3 MCU-side logical pads ONLY,"NO sensor connector, NO 5V sensor supply, NO approved module connection; level translation pending #2"
TP11,SENSOR_CS_3V3,PCB pad,TestPoint:TestPoint_Pad_D1.0mm,Bottom SMT,3V3 MCU-side logical pads ONLY,"NO sensor connector, NO 5V sensor supply, NO approved module connection; level translation pending #2"
TP12,SENSOR_SCLK_3V3,PCB pad,TestPoint:TestPoint_Pad_D1.0mm,Bottom SMT,3V3 MCU-side logical pads ONLY,"NO sensor connector, NO 5V sensor supply, NO approved module connection; level translation pending #2"
TP13,SENSOR_MOSI_3V3,PCB pad,TestPoint:TestPoint_Pad_D1.0mm,Bottom SMT,3V3 MCU-side logical pads ONLY,"NO sensor connector, NO 5V sensor supply, NO approved module connection; level translation pending #2"
TP14,SENSOR_MOTION_3V3,PCB pad,TestPoint:TestPoint_Pad_D1.0mm,Bottom SMT,3V3 MCU-side logical pads ONLY,"NO sensor connector, NO 5V sensor supply, NO approved module connection; level translation pending #2"
TP15,SENSOR_RESET_3V3,PCB pad,TestPoint:TestPoint_Pad_D1.0mm,Bottom SMT,3V3 MCU-side logical pads ONLY,"NO sensor connector, NO 5V sensor supply, NO approved module connection; level translation pending #2"
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
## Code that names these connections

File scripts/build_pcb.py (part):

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keepout=[155,75,205,125] if args.keys==65 else [151.425,52.7,208.575,128.575]
ROW_GPIO=[4,5,6,7,8]; COL_GPIO=[9,10,11,12,13,14,15,16,17,18,19,20,21,22,26]
# Reserve hardware SPI0 GP0/1/2/3 before assigning the twenty matrix pins.
gpio={0:'SENSOR_MISO_3V3',1:'SENSOR_CS_3V3',2:'SENSOR_SCLK_3V3',3:'SENSOR_MOSI_3V3'}
gpio.update({n:f'ROW{i}' for i,n in enumerate(ROW_GPIO)})
gpio.update({n:f'COL{i}' for i,n in enumerate(COL_GPIO)})
if args.keys==62:gpio[COL_GPIO[7]]=None  # No switches remain in COL7 on this variant.
gpio.update({23:'SENSOR_MOTION_3V3',24:'SENSOR_RESET_3V3'})
u1={}
for p in pins('MCU_RaspberryPi:RP2040'):
    num=item(p,'number')[1]; name=item(p,'name')[1]
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res('R6','1k',('XOUT','XOUT_CRYSTAL'),(469.9,73.66),(186.5,71.8),90)
res('R7','27R',('QSPI_SCLK','QSPI_SCLK_FLASH'),(241.3,139.7),(188.2,66.1))
# 12MHz, CL=10pF; 15pF caps assume ~2.5pF parasitics and require oscillator bring-up.
part('Y1','Device:Crystal_GND24','ABM8-272-T3 12MHz CL10pF','Crystal:Crystal_SMD_3225-4Pin_3.2x2.5mm',{1:'XIN',2:'GND',3:'XOUT_CRYSTAL',4:'GND'},(520.7,73.66),(187.2,69),mpn='ABM8-272-T3',note='Confirm ESR/drive/startup on assembled board')
cap('C16','15pF','XIN',(500.38,116.84),(186.5,73.8))
cap('C17','15pF','XOUT_CRYSTAL',(541.02,116.84),(189,73.8))
for ref,net,x,schx in [('SW67','BOOT_SW',205.5,215.9),('SW68','RUN',165.5,139.7)]:
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
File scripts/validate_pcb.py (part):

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 coord.append({'id':k['id'],'switch':f'SW{i}','expected_stem_mm':expected,'actual_stem_mm':actual,'error_mm':delta})
netroot=ET.parse(R/'netlist.xml').getroot()
schnet={(n.attrib['ref'],n.attrib['pin']):net.attrib['name'].replace('/','{slash}') for net in netroot.find('nets') for n in net.findall('node')}
check({pin:net for (ref,pin),net in schnet.items() if ref=='DB1'}=={'1':'VBUS_USB','2':'USB_DM','3':'USB_DP','4':'GND'},'External C5-JSH netlist pinout differs from J1')
netdiff=[]
net_pad_counts=Counter(p.GetNetname() for f in fps.values() for p in f.Pads() if p.GetNumber())
for ref,f in fps.items():
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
